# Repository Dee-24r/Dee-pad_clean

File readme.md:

# Deepad

## Demo Videoss (2)!

### Type and scroll with QMK Firmware

https://github.com/user-attachments/assets/2e771e5b-e012-48fb-b1c1-769b4b42860d

### Git commands with Arduino code (malfunctioning)

https://github.com/user-attachments/assets/827a11e4-f2cd-4bd8-a843-9fae9b40dcb5

## Overview

<br>
 <br><br>
My macropad contains 5 key switches, a rotary encoder with a switch, an OLED display, and 3 RGB LEDs. It uses the [SEEED Xiao RP2040](https://wiki.seeedstudio.com/XIAO-RP2040/) microcontroller.

[Macropad Demo.mp4](Macropad%20Demo.mp4)

## Assembly Progress
So, I'm gonna re-3d print the case, because it ain't gonna fit with the buttons already soldered. This time, they won't have divided 19.05 key holes. Just a large hole, they all come from.

## Repo info

This repo contains the design files (electrical and cad) for deepad v.1.0, :) my macropad. I added the schematic and pcb designs (along with the (custom) symbol and footprint libraries used), the case and pcb cad designs (in .STEP files), gerber files for pcb production (gerber.zip), and the firmware for the macropad. There is also an image folder (If you're scooping around, this is what you should open - it contains screenshots of every important file/design, and so does this README).

[Go to cad files](deepad_cad/)<br>
[Go to firmware](deepad_firmware/)<br>
[Go to schematic and pcb](deepad_sch_and_pcb/)<br>
[View screenshot of all files](images/) This is where you want to go!

## Making my macropad - with pics
I tried to make this to be journal-like cuz I enjoyed doing it. I hope I was detailed enough!

Components I designed it with:
 <br><br>

- 1x unsoldered Seeed XIAO RP2040 - the microcontroller
- 5x MX-Style switches - basically keys (keyboard keys)
- 1x EC11 Rotary encoder - it's like a knob and produces rotational value
- 1x 0.91 inch OLED display - display screen
- 5x white blank DSA keycaps - keycaps for the keys
- 3x SK6812 MINI-E LEDs - these are rgb leds
- 4x M3x16mm screws - for screwing my top and bottom case together
- 4x M3x5mx4mm heatset inserts - same as last one - they go together
- 6x 1N4148 diodes -  for the keys

I began by designing the schematic and pcb: added all my components and wired them.

I assigned footprints and routed the PCB, and learned to use vias. I added edge cuts and exported my STEP file to use in Fusion 360.

And these are 3d views of the pcb (front and back)

BRUH! If you're thinking everything went smooth and step by step, This was not the case! :)

Fusion 360 was a hassle! It's not a bad software; I just didn't know how to use it. But I'm glad I learned.

I started by drawing rectangles for the base of my case, adding holes for the screws and then extruding the shape - outer part of the case is 13mm deep and the inner is 3mm thick. I then attached my PCB .step file to "project" (I had so much trouble understanding how this worked) but got through it anyways. I projected my base case (not recursion :|) to make my top case, which was also 3mm thick. I rounded all my edges a bit and then added the holes for the keys and other components. Finally I added the usb cutout and extruded all holes. I later came back to add a few text decorations to the design (creative enough -- chee!) Here's my full cad design:

Next stage was the firmware! You can open up [the firmware folder](deepad_firmware/) to see all the code. It conatins the keyboard.json, rules.mk, config.h, and keymap.c files (keymap.c will still be edited to match my key functions).

I used QMK MSYS to create the folder and then edited the code to match my keys and board. And that was it!

I've soldered most of the parts onto my board. I've actually made more progress after this picture. I'll update the repo later.

Everything I did, I did with the help of many friends in the stasis and blueprint channels, and with much *searching online and asking AI many many many questions*. I'm happy with my work and can't wait to start using it!!

## Macropad use
My first idea for the controls are Git commands in VSCode or any other IDE (e.g. buttons to stage, to commit, push, pull, and more). I plan to have the RGB LEDs indicate information like the status of your branch. Same for the OLED display.

I also would love to see what I can do with this when I hack up a game - (coming soon)! My macropad is made compatible with via, so I'll be using it for many things for sure.

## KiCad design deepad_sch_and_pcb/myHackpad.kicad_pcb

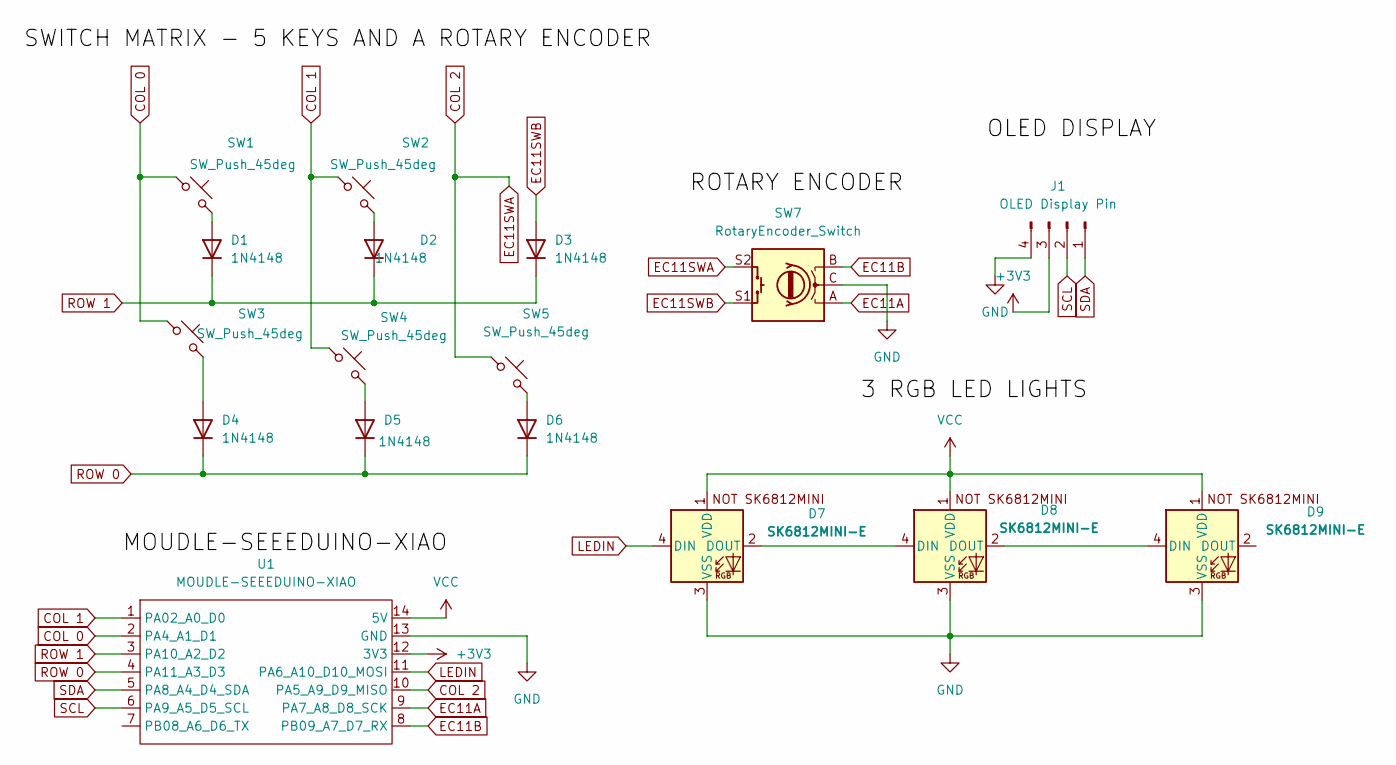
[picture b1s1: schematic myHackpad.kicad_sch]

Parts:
D1, D2, D3, D4, D5, D6: 1N4148; D_DO-35_SOD27_P7.62mm_Horizontal
D7, D8, D9: SK6812MINI-E; SK6812MINI-E_fixed
J1: OLED Display Pin; SSD1306-0.91-OLED-4pin-128x32
SW1, SW2, SW3, SW4, SW5: SW_Push_45deg; SW_Cherry_MX_1.00u_PCB
SW7: RotaryEncoder_Switch; RotaryEncoder_Alps_EC11E-Switch_Vertical_H20mm
U1: MOUDLE-SEEEDUINO-XIAO; XIAO-Generic-Hybrid-14P-2.54-21X17.8MM

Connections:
+3V3: J1.3, U1.12 (3V3)
COL 0: SW1.1, SW3.1, U1.2 (PA4_A1_D1)
COL 1: SW2.1, SW4.1, U1.1 (PA02_A0_D0)
COL 2: SW5.1, SW7.S2, U1.10 (PA5_A9_D9_MISO)
EC11A: SW7.A, U1.9 (PA7_A8_D8_SCK)
EC11B: SW7.B, U1.8 (PB09_A7_D7_RX)
EC11SWB: D3.2 (A), SW7.S1
GND: D7.3 (VSS), D8.3 (VSS), D9.3 (VSS), J1.4, SW7.C, U1.13 (GND)
LEDIN: D7.4 (DIN), U1.11 (PA6_A10_D10_MOSI)
unnamed: D1.2 (A), SW1.2
unnamed: D2.2 (A), SW2.2
unnamed: D4.2 (A), SW3.2
unnamed: D5.2 (A), SW4.2
unnamed: D6.2 (A), SW5.2
unnamed: D7.2 (DOUT), D8.4 (DIN)
unnamed: D8.2 (DOUT), D9.4 (DIN)
ROW 0: D4.1 (K), D5.1 (K), D6.1 (K), U1.4 (PA11_A3_D3)
ROW 1: D1.1 (K), D2.1 (K), D3.1 (K), U1.3 (PA10_A2_D2)
SCL: J1.2, U1.6 (PA9_A5_D5_SCL)
SDA: J1.1, U1.5 (PA8_A4_D4_SDA)
VCC: D7.1 (VDD), D8.1 (VDD), D9.1 (VDD), U1.14 (5V)

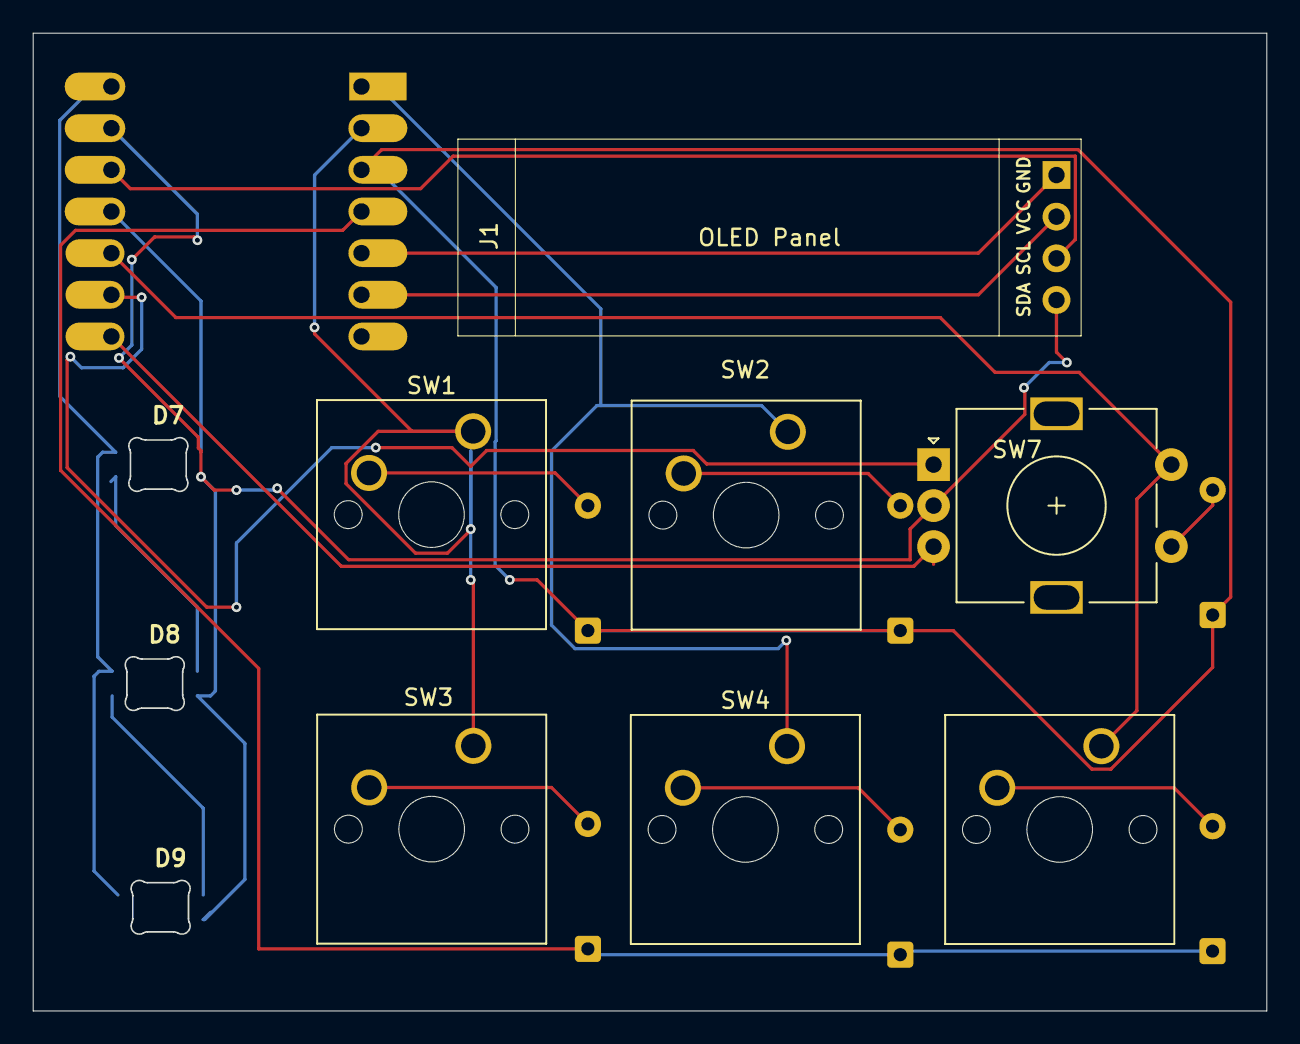
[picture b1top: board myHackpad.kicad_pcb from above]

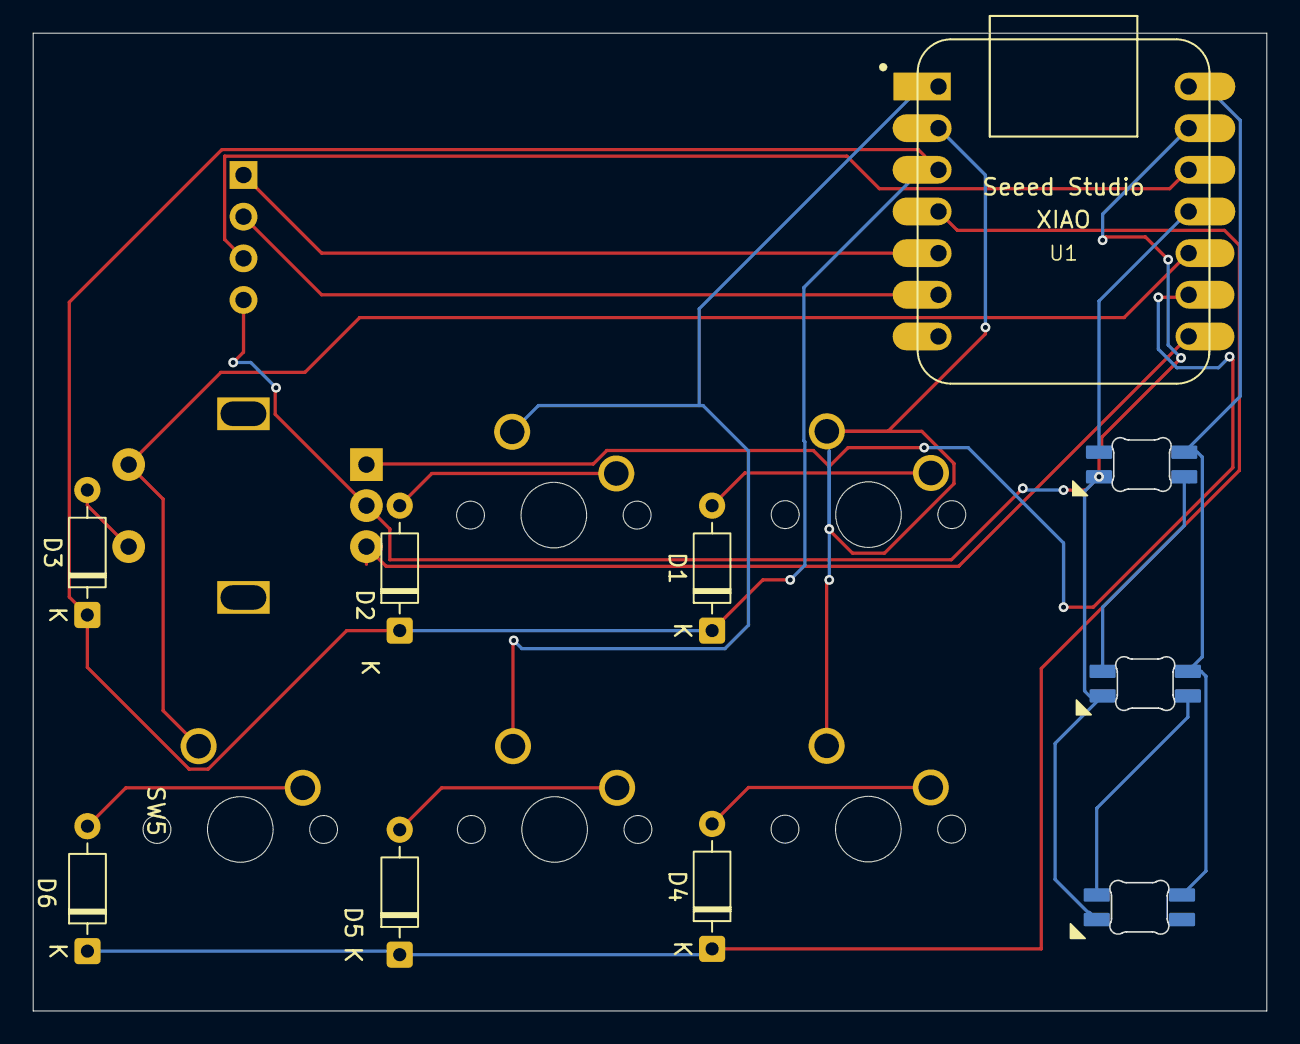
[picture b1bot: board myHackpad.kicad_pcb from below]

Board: 2 copper layers, 75.2 x 59.6 mm, 17 parts (7 on the bottom side), 21 nets.

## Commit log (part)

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2026-03-20 added all files
2026-03-20 images
2026-03-21 CAD design update and more files
2026-03-21 .wakatime-project file
2026-03-21 editing README
2026-03-21 readme again
2026-03-21 README edits
2026-03-21 readme
2026-03-21 README changes
2026-03-21 Changes in STEP files, added STL files
2026-03-21 BOM update
2026-03-21 Updated BOM
2026-03-22 Added diodes to BOM
2026-03-24 updated pcb pic
2026-04-01 changed top case and its stl file
2026-04-06 Journal
2026-04-15 image change
